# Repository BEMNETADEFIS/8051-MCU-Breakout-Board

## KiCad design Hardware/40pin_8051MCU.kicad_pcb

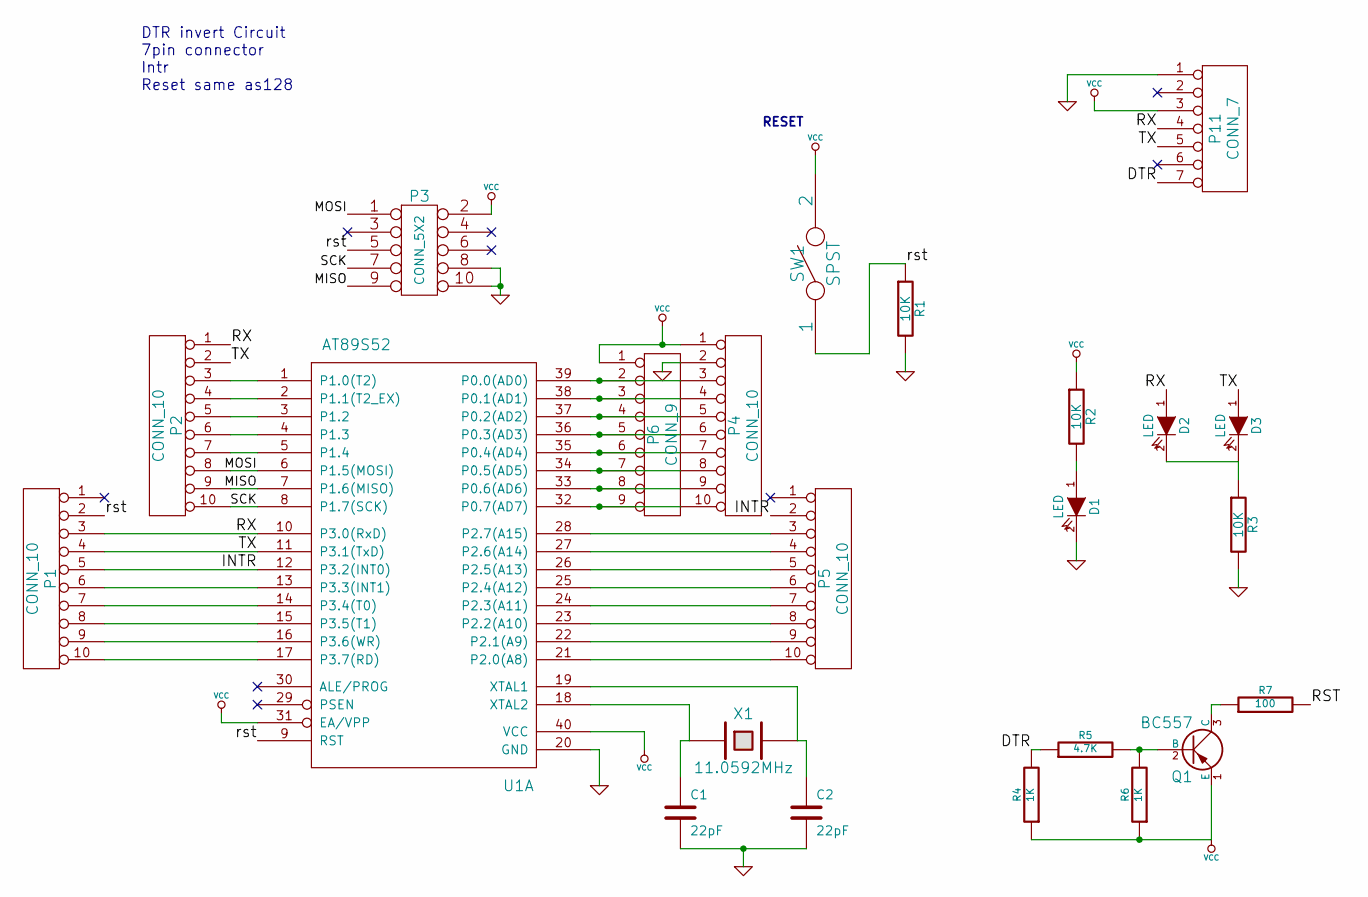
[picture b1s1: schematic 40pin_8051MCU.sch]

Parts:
C1, C2: 22pF
D1, D2, D3: LED
P1, P2, P4, P5: CONN_10
P3: CONN_5X2
P6: CONN_9
P11: CONN_7
Q1: BC557
R1, R2, R3: 10K
R4, R6: 1K
R5: 4.7K
R7: 100
SW1: SPST
U1: AT89S52
X1: 11.0592MHz

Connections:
/DTR: P11.7, R4.2, R5.1
/INTR: P1.5, P5.2, U1.12 (P3.2(INT0))
/MISO: P2.9, P3.9, U1.7 (P1.6(MISO))
/MOSI: P2.8, P3.1, U1.6 (P1.5(MOSI))
/RST: P1.2, P3.5, R1.1, R7.2, SW1.1, U1.9 (RST)
/RX: D2.1 (A), P1.3, P2.1, P11.4, U1.10 (P3.0(RxD))
/SCK: P2.10, P3.7, U1.8 (P1.7(SCK))
/TX: D3.1 (A), P1.4, P2.2, P11.5, U1.11 (P3.1(TxD))
GND: C1.2, C2.2, D1.2 (K), P3.8, P3.10, P4.2, P11.1, R1.2, R3.2, U1.20 (GND)
unnamed: D1.1 (A), R2.2
unnamed: D2.2 (K), D3.2 (K), R3.1
unnamed: P4.4, P6.3, U1.38 (P0.1(AD1))
unnamed: P4.3, P6.2, U1.39 (P0.0(AD0))
unnamed: P4.5, P6.4, U1.37 (P0.2(AD2))
unnamed: Q1.3 (C), R7.1
unnamed: Q1.2 (B), R5.2, R6.2
unnamed: P4.10, P6.9, U1.32 (P0.7(AD7))
unnamed: P4.9, P6.8, U1.33 (P0.6(AD6))
unnamed: P4.8, P6.7, U1.34 (P0.5(AD5))
unnamed: P4.7, P6.6, U1.35 (P0.4(AD4))
unnamed: P4.6, P6.5, U1.36 (P0.3(AD3))
unnamed: C2.1, U1.19 (XTAL1), X1.2
unnamed: C1.1, U1.18 (XTAL2), X1.1
unnamed: P5.3, U1.28 (P2.7(A15))
unnamed: P1.10, U1.17 (P3.7(RD))
unnamed: P2.6, U1.4 (P1.3)
unnamed: P2.5, U1.3 (P1.2)
unnamed: P2.4, U1.2 (P1.1(T2_EX))
unnamed: P2.3, U1.1 (P1.0(T2))
unnamed: P1.9, U1.16 (P3.6(WR))
unnamed: P1.8, U1.15 (P3.5(T1))
unnamed: P2.7, U1.5 (P1.4)
unnamed: P5.10, U1.21 (P2.0(A8))
unnamed: P5.9, U1.22 (P2.1(A9))
unnamed: P5.8, U1.23 (P2.2(A10))
unnamed: P5.7, U1.24 (P2.3(A11))
unnamed: P5.6, U1.25 (P2.4(A12))
unnamed: P5.5, U1.26 (P2.5(A13))
unnamed: P5.4, U1.27 (P2.6(A14))
unnamed: P1.6, U1.13 (P3.3(INT1))
unnamed: P1.7, U1.14 (P3.4(T0))
VCC: P3.2, P4.1, P6.1, P11.3, Q1.1 (E), R2.1, R4.1, R6.1, SW1.2, U1.31 (EA/VPP), U1.40 (VCC)

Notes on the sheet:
RESET
DTR invert Circuit 7pin connector Intr Reset same as128

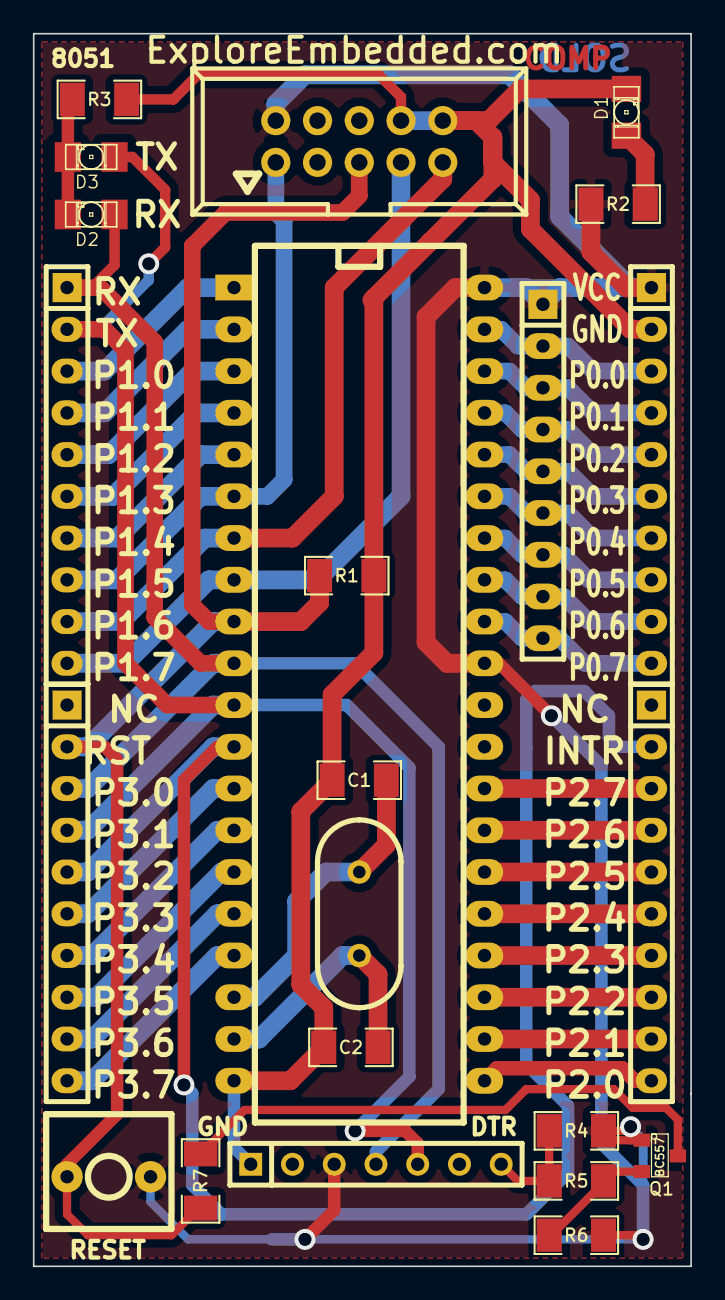
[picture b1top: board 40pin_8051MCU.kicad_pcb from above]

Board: 2 copper layers, 40.0 x 75.0 mm, 23 parts (0 on the bottom side), 42 nets.

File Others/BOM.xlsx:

Id | Designator | Package | Quantity | Designation | Supplier and ref
1 | P3 | VASCH5x2 | 1 | CONN_5X2
2 | SW1 | SW_PUSH_SMALL_2pin_xl | 1 | SPST
3 | P2,P1,P5,P4 | SIL-10 | 4 | CONN_10
4 | C1,C2 | SM1206 | 2 | 22pF
5 | R1,R2,R3 | SM1206 | 3 | 10K
6 | U1 | DIP-40__600_ELL | 1 | AT89S52
7 | D1,D2,D3 | LED-1206 | 3 | LED
8 | X1 | HC-49V | 1 | 11.0592MHz
9 | P6 | SIL-9 | 1 | CONN_9
10 | Q1 | SOT23 | 1 | BC557
11 | R5 | SM1206 | 1 | 4.7K
12 | R6,R4 | SM1206 | 2 | 1K
13 | R7 | SM1206 | 1 | 100
14 | P11 | SIL-7 | 1 | CONN_7

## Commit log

2015-06-02 added design files
2015-06-02 added files
